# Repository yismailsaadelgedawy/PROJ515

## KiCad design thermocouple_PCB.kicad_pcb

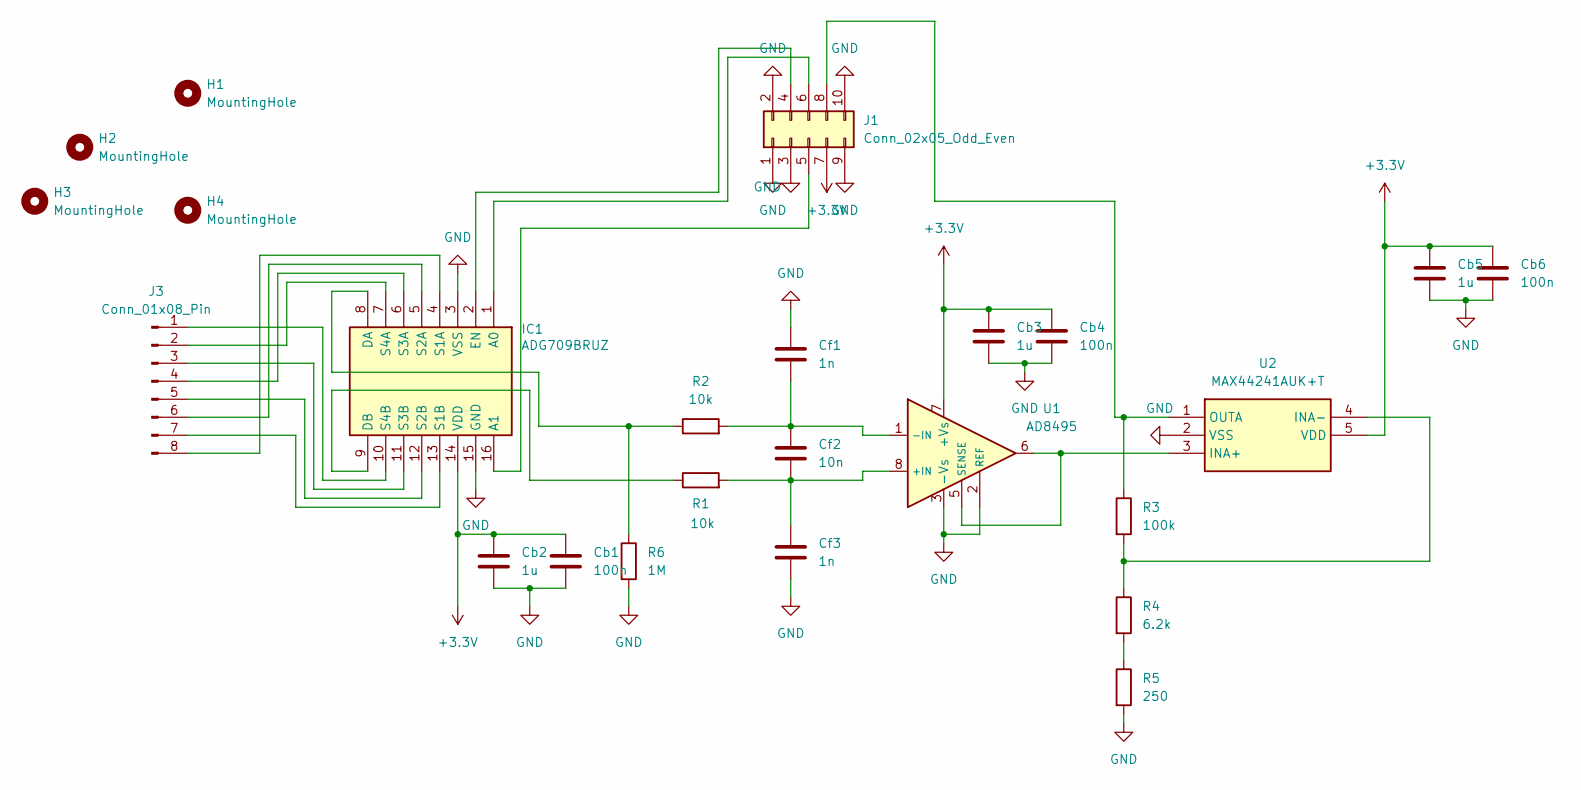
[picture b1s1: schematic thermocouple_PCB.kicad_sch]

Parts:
Cb1, Cb4, Cb6: 100n; C_0402_1005Metric
Cb2, Cb3, Cb5: 1u; C_0402_1005Metric
Cf1, Cf3: 1n; C_0603_1608Metric
Cf2: 10n; C_0603_1608Metric
H1, H2, H3, H4: MountingHole; MountingHole_2.2mm_M2_DIN965_Pad_TopBottom
IC1: ADG709BRUZ; TSSOP-16_4.4x5mm_P0.65mm; Manufacturer_Part_Number ADG709BRUZ; Mouser Part Number 584-ADG709BRUZ
J1: Conn_02x05_Odd_Even; PinHeader_2x05_P2.54mm_Horizontal
J3: Conn_01x08_Pin; PinHeader_1x08_P2.54mm_Horizontal
R1, R2: 10k; R_0402_1005Metric
R3: 100k; R_0402_1005Metric
R4: 6.2k; R_0603_1608Metric
R5: 250; R_0402_1005Metric
R6: 1M; R_0402_1005Metric
U1: AD8495; MSOP-8_3x3mm_P0.65mm
U2: MAX44241AUK+T; SOT-23-5; Manufacturer_Part_Number MAX44241AUK+T; Mouser Part Number 700-MAX44241AUK+T

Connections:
+3.3V: Cb1.1, Cb2.1, Cb3.1, Cb4.1, Cb5.1, Cb6.1, IC1.14 (VDD), J1.7, U1.7 (+Vs), U2.5 (VDD)
GND: Cb1.2, Cb2.2, Cb3.2, Cb4.2, Cb5.2, Cb6.2, Cf1.1, Cf3.2, IC1.3 (VSS), IC1.15 (GND), J1.1, J1.2, J1.3, J1.9, J1.10, R5.2, R6.2, U1.2 (REF), U1.3 (-Vs), U2.2 (VSS)
unnamed: IC1.1 (A0), J1.6
unnamed: IC1.16 (A1), J1.5
unnamed: IC1.8 (DA), R2.1, R6.1
unnamed: IC1.9 (DB), R1.1
unnamed: IC1.2 (EN), J1.4
unnamed: IC1.4 (S1A), J3.8
unnamed: IC1.13 (S1B), J3.7
unnamed: IC1.5 (S2A), J3.6
unnamed: IC1.12 (S2B), J3.5
unnamed: IC1.6 (S3A), J3.4
unnamed: IC1.11 (S3B), J3.3
unnamed: IC1.7 (S4A), J3.2
unnamed: IC1.10 (S4B), J3.1
unnamed: J1.8, R3.1, U2.1 (OUTA)
unnamed: R4.2, R5.1
unnamed: Cf2.2, Cf3.1, R1.2, U1.8 (+IN)
unnamed: Cf1.2, Cf2.1, R2.2, U1.1 (-IN)
unnamed: U1.5 (SENSE), U1.6, U2.3 (INA+)
unnamed: R3.2, R4.1, U2.4 (INA-)

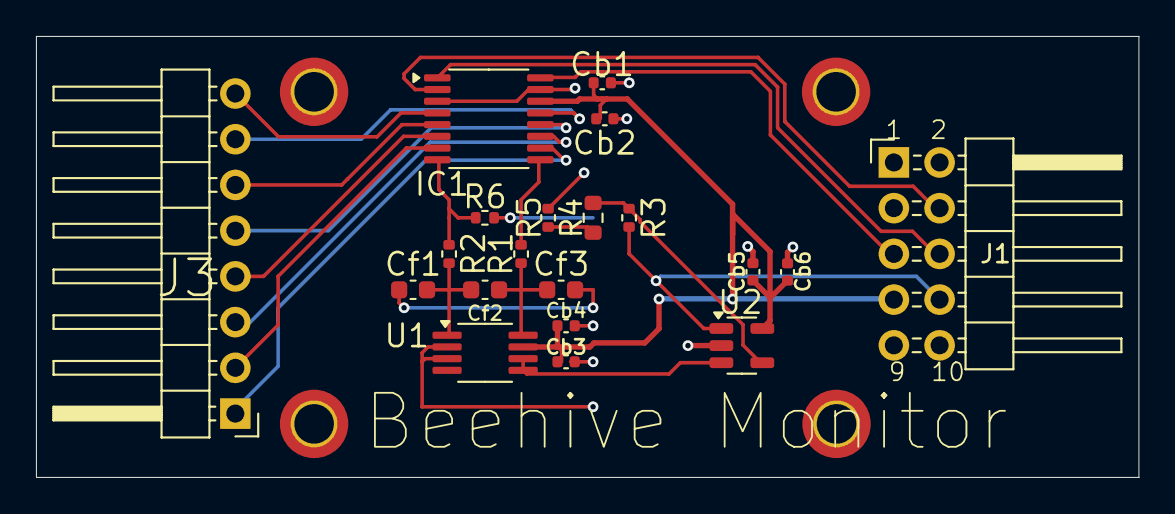
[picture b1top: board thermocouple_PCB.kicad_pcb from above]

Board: 2 copper layers, 61.2 x 24.5 mm, 24 parts (0 on the bottom side), 21 nets.

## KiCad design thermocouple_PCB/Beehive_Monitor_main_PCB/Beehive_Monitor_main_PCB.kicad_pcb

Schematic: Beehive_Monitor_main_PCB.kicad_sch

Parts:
5_V_PWR1, 12_V_PWR2: Conn_01x02_Pin; Molex_KK-254_AE-6410-02A_1x02_P2.54mm_Vertical
Accelerometer1: Conn_02x05_Odd_Even; PinHeader_2x05_P2.54mm_Vertical
C1: 22u; C_1206_3216Metric
C2, C11, C14, C25, C30, C35, C50, C51, C52, C101: 10u; C_0805_2012Metric
C3: 4.7u; C_1206_3216Metric
C4: 470n; C_0603_1608Metric
C5: 820p; C_0603_1608Metric_Pad1.08x0.95mm_HandSolder
C6: 68n; C_1206_3216Metric_Pad1.33x1.80mm_HandSolder
C7: 120p; C_0603_1608Metric_Pad1.08x0.95mm_HandSolder
C8, C9, C10, C18, C19, C20: 100u; C_1206_3216Metric
C12, C13, C24, C26, C32, C37, C41, C43, C45, C47, C49, C56, C80, C90, C92, C97, C98, C100, C103, C105, C107, C109, C114: 100n; C_0402_1005Metric
C15, C16, C17, C53, C54, C65, C72, C73, C74, C75, C76, C77: 15n; C_0805_2012Metric
C23, C40, C42, C44, C46, C48, C55, C57, C66, C78, C79, C81, C88, C89, C91, C93, C99, C102, C104, C106, C108, C110, C115: 1u; C_0402_1005Metric
C27, C33, C38: 3.3u; C_0603_1608Metric_Pad1.08x0.95mm_HandSolder
C28, C34, C39: 56p; C_0603_1608Metric_Pad1.08x0.95mm_HandSolder
C29, C31, C36: 2.2u; C_0603_1608Metric
C58, C59, C60, C61, C62, C63: 1.5n; C_0603_1608Metric
C64, C67, C69, C71: 1u; C_0402_1005Metric_Pad0.74x0.62mm_HandSolder
C68, C70: 100n; C_0402_1005Metric_Pad0.74x0.62mm_HandSolder
C82, C83, C84, C85, C86, C87, C111, C113, C116, C118: 10n; C_0603_1608Metric
C94, C96, C112, C117: 2.2n; C_0805_2012Metric
C95: 430p; C_0603_1608Metric_Pad1.08x0.95mm_HandSolder
Cboot1, Cboot5: 100n; C_0402_1005Metric
Css1, Css5: 2.2n; C_0805_2012Metric
D1, D2, D3, D4, D5, D7, D8: RBR2LAM60A; D_MELF
F1: Fuse; Fuseholder_Clip-5x20mm_Keystone_3517_Inline_P23.11x6.76mm_D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
IC1: LT6700HVCS6-3#PBF; TSOT-23-6; Manufacturer_Part_Number LT6700HVCS6-3#PBF
IC2, IC10: AD8226ARZ; SOIC-8_3.9x4.9mm_P1.27mm; Manufacturer_Part_Number AD8226ARZ; Mouser Part Number 584-AD8226ARZ
IC3, IC5: TPS54620RHLR; Texas_S-PVQFN-N14_ThermalVias; Manufacturer_Part_Number TPS54620RHLR; Mouser Part Number 595-TPS54620RHLR
IC4: AD8031ARTZ-R2; SOT-23-5; Manufacturer_Part_Number AD8031ARTZ-R2; Mouser Part Number 584-AD8031ARTZ-R2
IC6, IC7: MAX44246ASA+; MSOP-8_3x3mm_P0.65mm; Manufacturer_Part_Number MAX44246ASA+; Mouser Part Number 700-MAX44246ASA+
IC8: ADA4077-4ARZ; SOIC-14_3.9x8.7mm_P1.27mm; Manufacturer_Part_Number ADA4077-4ARZ; Mouser Part Number 584-ADA4077-4ARZ
IC9: SN74LV123ADRG4; TSSOP-16_4.4x5mm_P0.65mm; Manufacturer_Part_Number SN74LV123ADRG4; Mouser Part Number 595-SN74LV123ADRG4
IC11: TMUX1204DGSR; VSSOP-10_3x3mm_P0.5mm; Manufacturer_Part_Number TMUX1204DGSR; Mouser Part Number 595-TMUX1204DGSR
J1: Conn_02x08_Odd_Even; PinSocket_2x08_P2.54mm_Vertical_SMD
J2: Conn_02x10_Odd_Even; PinSocket_2x10_P2.54mm_Vertical_SMD
J3: Conn_02x15_Odd_Even; PinSocket_2x15_P2.54mm_Vertical_SMD
J4: Conn_02x17_Odd_Even; PinSocket_2x17_P2.54mm_Vertical_SMD
J5: Micro_SD_Card_Det_Hirose_DM3AT; microSD_HC_Hirose_DM3AT-SF-PEJM5
JP1: SolderJumper_2_Open; SolderJumper-2_P1.3mm_Open_RoundedPad1.0x1.5mm
JP3, JP4, JP5, JP7, JP8, JP9, JP10, JP11, JP12: SolderJumper_3_Bridged12; SolderJumper-3_P1.3mm_Bridged12_RoundedPad1.0x1.5mm
K2: HFD3_12-L2_257_; Relay_DPDT_Kemet_EC2_NU_DoubleCoil; Manufacturer_Part_Number HFD3/12-L2(257)
L1: 7443641000B; L_Wuerth_HCF-2818; Manufacturer_Part_Number 7443641000B; Mouser Part Number 710-7443641000B
L2: 22u; L_Wuerth_HCF-2818
L3: LMC555CMX_NOPB; SOIC-8_3.9x4.9mm_P1.27mm; Manufacturer_Part_Number LMC555CMX/NOPB; Mouser Part Number 926-LMC555CMX/NOPB
LCD_BTNs1: Conn_02x08_Odd_Even; PinHeader_2x08_P2.54mm_Vertical
LED_S1: Conn_02x05_Odd_Even; PinHeader_2x05_P2.54mm_Vertical
PE_9, PE_10, PE_15: SolderJumper_2_Open; SolderJumper-2_P1.3mm_Open_RoundedPad1.0x1.5mm
PF_14, PF_15: SolderJumper_2_Open; SolderJumper-2_P1.3mm_Open_RoundedPad1.0x1.5mm
PI_PWR1, PI_PWR2: Conn_01x02_Pin; Molex_KK-254_AE-6410-02A_1x02_P2.54mm_Vertical
PI_Ribbon1: Conn_02x05_Odd_Even; PinHeader_2x05_P2.54mm_Vertical
Q1, Q2, Q3, Q4, Q5, Q6, Q7: Q_NPN_BCE; SOT-23
Q8: PNP; SOT-23
Q9: FDS6681Z; SO-8_3.9x4.9mm_P1.27mm
R1, R3, R4, R17, R20, R28, R29, R30, R34, R35, R36, R39, R40, R41, R55, R72, R80, R87, R88, R105, R147, R148, R149, R500: 100k; R_0402_1005Metric
R2: 11.5k; R_0603_1608Metric_Pad0.98x0.95mm_HandSolder
R5, R73, R99, R103, R108, R123, R134, R140, R152, R169: 200; R_0402_1005Metric
R6, R15: 150k; R_0603_1608Metric
R7: 12k; R_0603_1608Metric_Pad0.98x0.95mm_HandSolder
R8, R119, R165, R175: 47k; R_0402_1005Metric
R9, R21, R44, R45, R96, R131, R168: 10k; R_0402_1005Metric
R10, R19: 3.9k; R_0603_1608Metric
R11: 330; R_0603_1608Metric
R12: 5.1k; R_0402_1005Metric
R13, R51: 150; R_0603_1608Metric
R14, R49, R65, R113, R129, R167: 12k; R_0603_1608Metric
R16: 909; R_0603_1608Metric_Pad0.98x0.95mm_HandSolder
R18, R89, R106, R151: 27k; R_0603_1608Metric
R22: 4.99k; R_0603_1608Metric
R23, R25, R42: 20k; R_0603_1608Metric_Pad0.98x0.95mm_HandSolder
R24, R26, R43: 5k; R_0603_1608Metric_Pad0.98x0.95mm_HandSolder
R27, R32, R37, R84, R92: 2.4k; R_0603_1608Metric
R31, R33, R38, R58, R68, R161, R172: 100; R_0603_1608Metric
R46: 1k; R_0402_1005Metric
R47, R116: 120k; R_0603_1608Metric
R48: 261k; R_0603_1608Metric_Pad0.98x0.95mm_HandSolder
R50, R81, R101, R157: 3k; R_0603_1608Metric
R52: 68.1k; R_0603_1608Metric_Pad0.98x0.95mm_HandSolder
R53: 37.4k; R_0603_1608Metric_Pad0.98x0.95mm_HandSolder
R54: 499; R_0603_1608Metric_Pad0.98x0.95mm_HandSolder
R56, R66, R82: 1.5k; R_0402_1005Metric
R57, R155, R160, R171: 2.2k; R_0603_1608Metric
R59: 56k; R_0603_1608Metric
R60, R162, R173: 75k; R_0603_1608Metric
R61, R90, R104: 470; R_0402_1005Metric
R62: 191k; R_0603_1608Metric_Pad0.98x0.95mm_HandSolder
R63: 41.7k; R_0603_1608Metric_Pad0.98x0.95mm_HandSolder
R64: 562; R_0603_1608Metric_Pad0.98x0.95mm_HandSolder
R67, R86, R91, R114, R164: 2k; R_0603_1608Metric
R69, R85, R95, R97, R132: 200k; R_0603_1608Metric
R70, R98, R133: 15k; R_0402_1005Metric
R71, R100, R135, R150: 1M; R_0402_1005Metric
R74, R111, R159, R163, R170, R174: 33k; R_0603_1608Metric
R75: 140k; R_0603_1608Metric_Pad0.98x0.95mm_HandSolder
R76: 1.2k; R_0603_1608Metric
R77, R145: 220; R_0603_1608Metric
R78: 316k; R_0603_1608Metric_Pad0.98x0.95mm_HandSolder
R79: 30k; R_0603_1608Metric
R83: 560; R_0603_1608Metric
R93, R136, R137: 220k; R_0603_1608Metric
R94, R156: 22k; R_0603_1608Metric
R102: 91k; R_0603_1608Metric_Pad0.98x0.95mm_HandSolder
R107: 6.34k; R_0603_1608Metric_Pad0.98x0.95mm_HandSolder
R109: 255k; R_0603_1608Metric_Pad0.98x0.95mm_HandSolder
R110, R141: 68k; R_0603_1608Metric
R112: 82k; R_0603_1608Metric
R115: 249; R_0603_1608Metric_Pad0.98x0.95mm_HandSolder
R117: 300k; R_0603_1608Metric
R118: 330k; R_0603_1608Metric
R120, R125, R126, R127, R138, R139, R142, R143: 4.7k; R_0402_1005Metric
R121, R130: 270; R_0603_1608Metric
R122: 80.6; R_0603_1608Metric_Pad0.98x0.95mm_HandSolder
R124: 4.32k; R_0603_1608Metric_Pad0.98x0.95mm_HandSolder
R128: 732k; R_0603_1608Metric_Pad0.98x0.95mm_HandSolder
R144, R146: 120; R_0402_1005Metric
R154: 6.2k; R_0603_1608Metric
R158: 18k; R_0603_1608Metric
R166, R176: 5.6k; R_0603_1608Metric
RV1, RV2: 5k; Potentiometer_Bourns_3296Y_Vertical
RV3, RV10, RV11: 50k; Potentiometer_Bourns_3296W_Vertical
RV4, RV5, RV6, RV7, RV8: 200k; Potentiometer_Bourns_3296W_Vertical
RV9: 25k; Potentiometer_Bourns_3296W_Vertical
TC_1_2, TC_3_4: Conn_02x07_Odd_Even; PinHeader_2x07_P2.54mm_Vertical
TP_1, TP_2, TP_3, TP_4, TP_5, TP_6, TP_7, TP_8, TP_9, TP_10: Conn_01x01_Pin; PinHeader_1x01_P2.54mm_Vertical
U1, U3, U4, U6, U7, U8: Opamp_Quad; SOIC-14_3.9x8.7mm_P1.27mm
U2, U5: TLV3201/2; SOIC-8_3.9x4.9mm_P1.27mm
mic_1_LDR1: Conn_01x04_Pin; Molex_KK-254_AE-6410-04A_1x04_P2.54mm_Vertical
mic_2: Conn_01x02_Pin; Molex_KK-254_AE-6410-02A_1x02_P2.54mm_Vertical

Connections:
3.3_V_out: C18.1, C19.1, C20.1, J1.8, K2.4 (COM_1), L2.2, LED_S1.10, PI_PWR2.1, R18.1; also elsewhere on the board
5_V: 5_V_PWR1.1, C8.1, C9.1, C10.1, C99.1, C100.1, D7.1 (K), D8.1 (K), IC9.2 (1B), IC9.3 (1~CLR), IC9.11 (2~CLR), IC9.16 (VCC), JP1.1 (A), K2.1 (SET+), K2.6 (RESET+), L1.1, LED_S1.4, LED_S1.6, PI_PWR1.1, Q8.3 (E), R8.1, R131.1, R136.1, R137.2, R144.1; also elsewhere on the board
6.11_kHz_AA_out_MCU: C63.2, D1.2 (A), J3.25, R63.2, R67.2, U1.14
6.11_kHz_out_MCU: J2.19, PI_Ribbon1.9, R71.2, U2.1; also elsewhere on the board
240_Hz_out_MCU: J2.11, PI_Ribbon1.1, R100.2, U2.7; also elsewhere on the board
555_out: L3.3 (OUTPUT), R146.1
Acc_420_Hz_out_MCU: J2.9, R135.2, U5.1
Acc_AA_out_to_MCU: C96.2, J3.2, U6.8, U6.9 (-)
Acc_sig_in: Accelerometer1.3, C35.1, C36.1; also elsewhere on the board
Acc_tmp: Accelerometer1.8, J4.12; also elsewhere on the board
BTN_1: J3.18, LCD_BTNs1.5; also elsewhere on the board
BTN_2: J3.20, LCD_BTNs1.3; also elsewhere on the board
BTN_3: J3.22, LCD_BTNs1.1; also elsewhere on the board
Cref: R72.1, RV7.3, TP_8.1, U2.2 (-), U2.6 (-)
Cref2: R167.1, RV8.3, TP_9.1, U5.2 (-)
D_4: J3.7, LCD_BTNs1.13; also elsewhere on the board
D_5: J3.5, LCD_BTNs1.11; also elsewhere on the board
D_6: J3.3, LCD_BTNs1.9; also elsewhere on the board
D_7: J3.1, LCD_BTNs1.7; also elsewhere on the board
EN: J4.20, LCD_BTNs1.12; also elsewhere on the board
Front_mic_pin: C30.1, C31.1, mic_1_LDR1.1; also elsewhere on the board
GND: 5_V_PWR1.2, 12_V_PWR2.2, Accelerometer1.9, C1.2, C2.2, C3.2, C4.2, C5.2, C6.2, C7.2, C8.2, C9.2, C10.2, C11.2, C12.2, C13.2, C14.2, C18.2, C19.2, C20.2, C23.2, C24.2, C26.2, C27.2, C32.2, C33.2, C37.2, C38.2, C40.2, C41.2, C42.2, C43.2, C44.2, C45.2, C46.2, C47.2, C48.2, C49.2, C50.2, C51.2, C52.2, C55.2, C56.2, C57.1, C64.2, C66.2, C67.2, C68.2, C69.2, C70.2, C71.1, C78.2, C79.2, C80.2, C81.1, C88.2, C89.2, C90.2, C91.2, C92.2, C99.2, C100.2, C101.2, C102.2, C103.2, C104.2, C105.2, C106.2, C107.2, C108.2, C109.2, C114.2, Css1.2, Css5.2, IC1.2 (GND), IC2.5 (-VS), IC2.6 (REF), IC3.2 (GND_1), IC3.3 (GND_2), IC3.15 (EP), IC4.2 (-VS), IC5.2 (GND_1), IC5.3 (GND_2), IC5.15 (EP), IC6.4 (GND), IC7.4 (GND), IC7.5 (INB+), IC8.11 (V-), IC9.8 (GND), IC9.9 (2~A), IC10.5 (-VS), IC10.6 (REF), IC11.3 (GND), J1.12, J1.14, J2.7, J3.11, J3.24, J4.6, J4.18, J4.21, J4.28, J5.6 (VSS), J5.11 (SHIELD), JP3.1 (A), JP4.1 (A), JP5.1 (A), JP7.1 (A), JP8.1 (A), JP9.1 (A), JP10.1 (A), JP11.1 (A), JP12.1 (A), L3.1 (GND), LCD_BTNs1.16, PI_PWR1.2, PI_PWR2.2, Q1.3 (E), Q2.3 (E), Q4.3 (E), Q5.3 (E), Q6.3 (E), R7.1, R9.2, R14.1, R20.2, R21.2, R29.2, R35.2, R40.2, R69.2, R97.2, R132.2, R145.2, R148.2, R152.2, RV1.2, RV2.2, RV7.2, RV8.2, RV9.2, RV11.2, TC_1_2.2, TC_1_2.13, TC_3_4.2, TC_3_4.13, U1.11 (V-), U2.4 (V-), U3.11 (V-), U4.11 (V-), U5.4 (V-), U6.11 (V-), U6.12 (+), U7.11 (V-), U7.12 (+), U8.11 (V-), U8.12 (+), mic_1_LDR1.2, mic_2.2; also elsewhere on the board
IC6_inA+: C32.1, C33.1, IC6.3 (INA+), R34.2, R35.1
IC6_inA-: C34.1, IC6.2 (INA-), R33.2, R36.1
IC6_inB+: C26.1, C27.1, IC6.5 (INB+), R28.2, R29.1
IC6_inB-: C28.1, IC6.6 (INB-), R30.1, R31.2
IC6_outA: C34.2, IC6.1 (OUTA), IC8.3 (+IN_A), R36.2
IC6_outB: C28.2, IC6.7 (OUTB), IC8.5 (+IN_B), R30.2
IC7_inA+: C37.1, C38.1, IC7.3 (INA+), R39.2, R40.1
IC7_inA-: C39.1, IC7.2 (INA-), R38.2, R41.1
IC7_outA: C39.2, IC7.1 (OUTA), IC8.10 (+IN_C), R41.2
LCD_B/light: J3.30, LCD_BTNs1.2; also elsewhere on the board
LDR_TRIG_out_MCU: J2.17, PI_Ribbon1.7, R150.2, U5.7; also elsewhere on the board
LDR_out_MCU: IC10.7 (VOUT), J3.12, R151.1, TP_10.1
LDR_pin_1: Accelerometer1.2, C23.1, C24.1, C40.1, C41.1, C42.1, C43.1, C44.1, C45.1, C48.1, C49.1, C55.1, C56.1, C66.1, C67.1, C68.1, C69.1, C70.1, C79.1, C80.1, C89.1, C90.1, C91.1, C92.1, C104.1, C105.1, C106.1, C107.1, C108.1, C109.1, C114.1, IC2.8 (+VS), IC4.5 (+VS), IC6.8 (VDD), IC7.8 (VDD), IC8.4 (V+), IC10.8 (+VS), IC11.5 (EN), IC11.6 (VDD), IC11.8 (D), J5.4 (VDD), K2.3 (NC_1), LCD_BTNs1.4, LCD_BTNs1.6, LCD_BTNs1.8, LCD_BTNs1.10, R4.1, R17.1, R28.1, R34.1, R39.1, R72.2, R110.2, R147.1, R149.1, TC_1_2.5, TC_1_2.10, TC_3_4.5, TC_3_4.10, U1.4 (V+), U2.8 (V+), U3.4 (V+), U4.4 (V+), U5.8 (V+), U6.4 (V+), U7.4 (V+), U8.4 (V+), mic_1_LDR1.3; also elsewhere on the board
LDR_pin_2: IC10.4 (+IN), RV9.1, TP_7.1, mic_1_LDR1.4; also elsewhere on the board
LNA_Acc_out: IC8.8 (OUT_C), RV6.1, TP_6.1, U4.3 (+), U6.3 (+)
LNA_MF_out: IC8.1 (OUT_A), R44.1, RV4.1, TP_4.1, U1.3 (+), U3.3 (+), U8.3 (+)
LNA_MR_out: IC8.7 (OUT_B), RV5.1, TP_5.1, U7.3 (+)
MCU_LED_IN: J3.21, R120.1, R125.1
MCU_TC_add_0: J1.13, TC_1_2.1, TC_1_2.14, TC_3_4.1, TC_3_4.14
MCU_TC_add_1: J1.15, TC_1_2.4, TC_1_2.11, TC_3_4.4, TC_3_4.11
MCU_TC_add_2: IC11.1 (A0), J3.26
MCU_TC_add_3: IC11.10 (A1), J3.28
M_LED_1_cathode: LED_S1.3, R121.1; also elsewhere on the board
M_LED_2_cathode: LED_S1.5, R130.1; also elsewhere on the board
Maintainance _int: J4.1, LED_S1.9, PI_Ribbon1.10; also elsewhere on the board
Mic_F_AA_out_to_MCU: C113.2, J3.4, U8.8, U8.9 (-)
Mic_R_AA_out_to_MCU: C118.2, J3.6, U7.8, U7.9 (-)
Mic_out_to_AA: IC8.14 (OUT_D), R45.1
unnamed: 12_V_PWR2.1, F1.1
unnamed: C4.1, R16.2
unnamed: C6.1, R11.2
unnamed: C15.1, C16.1, C76.1, C77.1, R89.1, R90.2
unnamed: C17.1, C53.1, C74.1, C75.1, R81.2, R82.1
unnamed: C17.2, C75.2, R86.2, R87.1, R88.2, U3.8
unnamed: C25.2, C29.2, R27.1
unnamed: C30.2, C31.2, R32.1
unnamed: C35.2, C36.2, R37.1
unnamed: C50.1, R24.2
unnamed: C51.1, R26.2
unnamed: C52.1, R43.2
unnamed: C54.1, C65.1, C72.1, C73.1, R75.2, R76.1
unnamed: C58.1, C59.1, R46.1, R47.2
unnamed: C59.2, R50.1, R52.1, U1.7
unnamed: C60.1, C61.1, R56.1, R57.2
unnamed: C61.2, R53.1, R59.2, R60.2, U1.8
unnamed: C62.1, C63.1, R61.2, R65.1
unnamed: C65.2, C73.2, R79.1, R80.1, U3.7
unnamed: C82.1, C83.1, R106.2, R107.1
unnamed: C83.2, R109.1, R111.1, U4.7
unnamed: C84.1, C85.1, R113.2, R114.1
unnamed: C85.2, R119.2, R122.2, U4.8
unnamed: C86.1, C87.1, R123.1, R124.2
unnamed: C96.1, R117.1, R157.2
unnamed: C113.1, R163.2, R165.1
unnamed: C118.1, R174.2, R175.1
unnamed: C64.1, D1.1 (K), R69.1, R70.1
unnamed: C16.2, C77.2, D2.2 (A), R94.2, R96.2, U3.14
unnamed: C78.1, D2.1 (K), R97.1, R98.1
unnamed: C87.2, D3.2 (A), R129.2, U4.14
unnamed: C88.1, D3.1 (K), R132.1, R133.1
unnamed: D5.2 (A), R146.2
unnamed: D7.2 (A), K2.12 (SET-), Q6.2 (C)
unnamed: D8.2 (A), K2.7 (RESET-), Q5.2 (C)
unnamed: IC1.3 (+INA), R13.2, RV1.3
unnamed: IC1.4 (+INB), R3.2, RV2.3
unnamed: IC2.2 (RG_1), RV3.2
unnamed: IC2.3 (RG_2), RV3.1
unnamed: Cboot5.1, IC3.13 (BOOT)
unnamed: C7.1, IC3.8 (COMP), R10.1
unnamed: Cboot5.2, IC3.11 (PH_1), IC3.12 (PH_2), L1.2
unnamed: IC3.1 (RT/CLK), R6.2
unnamed: Css5.1, IC3.9 (SS/TR)
unnamed: C11.1, C12.1, IC4.3 (+IN), R17.2, R20.1
unnamed: IC4.4 (-IN), R22.1
unnamed: Cboot1.1, IC5.13 (BOOT)
unnamed: C5.1, IC5.8 (COMP), R16.1
unnamed: Cboot1.2, IC5.11 (PH_1), IC5.12 (PH_2), L2.1
unnamed: IC5.1 (RT/CLK), R15.2
unnamed: Css1.1, IC5.9 (SS/TR)
unnamed: IC7.6 (INB-), IC7.7 (OUTB)
unnamed: IC8.2 (-IN_A), R23.2, R24.1
unnamed: IC8.6 (-IN_B), R25.2, R26.1
unnamed: IC8.9 (-IN_C), R42.2, R43.1
unnamed: IC8.13 (-IN_D), R44.2, R45.2
unnamed: C98.1, IC9.14 (1CEXT)
unnamed: C98.2, IC9.15 (1REXT/CEXT), R137.1
unnamed: IC9.1 (1~A), IC9.10 (2B), Q3.2 (C), R131.2
unnamed: C97.2, IC9.6 (2CEXT)
unnamed: C97.1, IC9.7 (2REXT/CEXT), R136.2
unnamed: IC10.1 (-IN), R147.2, R148.1
unnamed: IC10.2 (RG_1), RV10.1
unnamed: IC10.3 (RG_2), RV10.2
unnamed: J1.10, JP1.2 (B)
unnamed: J4.3, PE_9.1 (A)
unnamed: J4.7, PF_14.1 (A)
unnamed: J4.11, PF_15.1 (A)
unnamed: J4.23, PE_10.1 (A)
unnamed: J4.29, PE_15.1 (A)
unnamed: C110.2, JP3.2 (C)
unnamed: C111.2, JP4.2 (C)
unnamed: C115.2, JP5.2 (C)
unnamed: C112.2, JP7.2 (C)
unnamed: C116.2, JP8.2 (C)
unnamed: C117.2, JP9.2 (C)
unnamed: C93.2, JP10.2 (C)
unnamed: C94.2, JP11.2 (C)
unnamed: C95.2, JP12.2 (C)
unnamed: L3.7 (DISCHARGE), R141.1, R169.2
unnamed: C101.1, L3.2 (~TRIGGER), L3.6 (THRESHOLD), R164.2
unnamed: Q1.1 (B), R120.2
unnamed: Q1.2 (C), R121.2
unnamed: Q2.1 (B), R126.2
unnamed: Q2.2 (C), R130.2
unnamed: Q3.1 (B), R125.2
unnamed: Q3.3 (E), Q4.2 (C)
unnamed: Q4.1 (B), R127.2
unnamed: Q5.1 (B), R139.2
unnamed: Q6.1 (B), R138.2
unnamed: Q7.1 (B), R142.2
unnamed: Q7.2 (C), R144.2
unnamed: Q8.2 (B), R143.2
unnamed 144: F1.2, Q9.1 (D); also elsewhere on the board
unnamed: Q9.2 (G), R152.1
unnamed: R6.1, R7.2
unnamed: R10.2, R11.1
unnamed: R8.2, R12.1
unnamed: R5.1, R12.2
unnamed: R2.2, R13.1
unnamed: R14.2, R15.1
unnamed: R18.2, R19.1
unnamed: R23.1, RV4.2
unnamed: R25.1, RV5.2
unnamed: R27.2, R31.1
unnamed: R32.2, R33.1
unnamed: R37.2, R38.1
unnamed: R42.1, RV6.2
unnamed: R46.2, R51.2
unnamed: R47.1, R49.2
unnamed: R48.1, R50.2
unnamed: R52.2, R57.1
unnamed: R55.2, R59.1
unnamed: R56.2, R58.1
unnamed: R60.1, R65.2
unnamed: R61.1, R66.2
unnamed: R62.2, R67.1
unnamed: R63.1, R68.2
unnamed: R70.2, R73.1
unnamed: R74.2, R75.1
unnamed: R76.2, R77.2
unnamed: R78.1, R79.2
unnamed: R82.2, R83.1
unnamed: R85.2, R86.1
unnamed: R88.1, R89.2
unnamed: R90.1, R91.2
unnamed: R93.2, R94.1
unnamed: R95.2, R96.1
unnamed: R98.2, R99.1
unnamed: R80.2, R101.1
unnamed: R81.1, R101.2
unnamed: R87.2, R102.1
unnamed: R84.2, R103.1
unnamed: R92.1, R104.2
unnamed: R105.2, R106.1
unnamed: R107.2, R108.2
unnamed: R110.1, R167.2
unnamed: R111.2, R113.1
unnamed: R112.2, R154.1
unnamed: R114.2, R115.1
unnamed: R116.2, R156.1
unnamed: R117.2, R158.1
unnamed: R118.2, R168.1
unnamed: R119.1, R168.2
unnamed: R122.1, R123.2
unnamed: R128.2, R129.1
unnamed: R133.2, R134.1
unnamed: R140.2, R169.1
unnamed: R141.2, R164.1
unnamed: R154.2, R155.1
unnamed: R156.2, R157.1
unnamed: R159.2, R160.1
unnamed: R160.2, R161.1
unnamed: R162.2, R163.1
unnamed: R165.2, R166.1
unnamed: R170.2, R171.1
unnamed: R171.2, R172.1
unnamed: R173.2, R174.1
unnamed: R175.2, R176.1
unnamed: C57.2, R49.1, U1.1, U1.2 (-)
unnamed: C58.2, R48.2, U1.6 (-)
unnamed: R53.2, R54.1, U1.10 (+)
unnamed: C60.2, R55.1, U1.9 (-)
unnamed: R64.2, R68.1, U1.12 (+)
unnamed: C62.2, R62.1, U1.13 (-)
unnamed: R71.1, R73.2, U2.3 (+)
unnamed: R99.2, R100.1, U2.5 (+)
unnamed: C71.2, R74.1, U3.1, U3.2 (-)
unnamed: C54.2, C72.2, R78.2, U3.6 (-)
unnamed: R84.1, R102.2, U3.10 (+)
unnamed: C53.2, C74.2, R85.1, U3.9 (-)
unnamed: R92.2, R95.1, U3.12 (+)
unnamed: C15.2, C76.2, R93.1, U3.13 (-)
unnamed: C81.2, R105.1, U4.1, U4.2 (-)
unnamed: C82.2, R109.2, U4.6 (-)
unnamed: C84.2, R118.1, U4.9 (-)
unnamed: C86.2, R128.1, U4.13 (-)
unnamed: R134.2, R135.1, U5.3 (+)
unnamed: R150.1, R151.2, U5.5 (+)
unnamed: R149.2, RV11.1, U5.6 (-)
unnamed: C93.1, R112.1, U6.1, U6.2 (-)
unnamed: C94.1, R155.2, U6.5 (+)
unnamed: R116.1, U6.6 (-), U6.7
unnamed: C95.1, R158.2, U6.10 (+)
unnamed: U6.13 (-), U6.14
unnamed: C115.1, R170.1, U7.1, U7.2 (-)
unnamed: C116.1, R172.2, U7.5 (+)
unnamed: R173.1, U7.6 (-), U7.7
unnamed: C117.1, R176.2, U7.10 (+)
unnamed: U7.13 (-), U7.14
unnamed: C110.1, R159.1, U8.1, U8.2 (-)
unnamed: C111.1, R161.2, U8.5 (+)
unnamed: R162.1, U8.6 (-), U8.7
unnamed: C112.1, R166.2, U8.10 (+)
unnamed: U8.13 (-), U8.14
PI_CS: J4.5, PI_Ribbon1.8; also elsewhere on the board
PI_LED_IN: PI_Ribbon1.3, R126.1, R127.1; also elsewhere on the board
PI_MISO: J4.9, PI_Ribbon1.6; also elsewhere on the board
PI_MOSI: J4.27, PI_Ribbon1.2; also elsewhere on the board
PI_SCLK: J4.25, PI_Ribbon1.4; also elsewhere on the board
Pwr_LED_Anode: D4.1 (K), D5.1 (K), LED_S1.2; also elsewhere on the board
Pwr_LED_Cathode: LED_S1.1, R145.1; also elsewhere on the board
RS: J4.24, LCD_BTNs1.14; also elsewhere on the board
RW: J4.22, LCD_BTNs1.15; also elsewhere on the board
Rear_mic_pin: C25.1, C29.1, mic_2.1; also elsewhere on the board
Relay_close: IC9.5 (2Q), R139.1
Relay_open: IC9.13 (1Q), R138.1
SD_CS: J2.14, J5.2 (DAT3/CD)
SD_MISO: J2.20, J5.7 (DAT0)
SD_MOSI: J2.16, J5.3 (CMD)
SD_SCLK: J2.18, J5.5 (CLK)
SD__detect: J4.16, J5.9 (DET_B), J5.10 (DET_A)
TC_EN_1: IC11.2 (S1), TC_1_2.3
TC_EN_2: IC11.9 (S2), TC_1_2.12
TC_EN_3: IC11.4 (S3), TC_3_4.3
TC_EN_4: IC11.7 (S4), TC_3_4.12
TC_Sig_1: J3.10, TC_1_2.6, TC_1_2.9, TC_3_4.6, TC_3_4.9
V_555: C102.1, C103.1, L3.4 (~RESET), L3.8 (V+), Q8.1 (C), R140.1
V_LED: D4.2 (A), Q7.3 (E)
Vcharge_MCU: IC2.7 (VOUT), J3.8, TP_3.1
Ven: IC1.6 (OUTB), IC3.10 (EN), IC5.10 (EN), R500.2, TP_1.1
Vref: C13.1, C14.1, IC2.4 (+IN), IC4.1 (VOUT), IC8.12 (+IN_D), JP3.3 (B), JP4.3 (B), JP5.3 (B), JP7.3 (B), JP8.3 (B), JP9.3 (B), JP10.3 (B), JP11.3 (B), JP12.3 (B), R22.2, R51.1, R54.2, R58.2, R64.1, R66.1, R77.1, R83.2, R91.1, R103.2, R104.1, R108.1, R115.2, R124.1, U1.5 (+), U3.5 (+), U4.5 (+), U4.10 (+), U4.12 (+)
Vreg_in: C1.1, C2.1, C3.1, C46.1, C47.1, IC1.5 (VS), IC3.4 (PVIN_1), IC3.5 (PVIN_2), IC3.6 (VIN), IC5.4 (PVIN_1), IC5.5 (PVIN_2), IC5.6 (VIN), Q9.3 (S), R1.1, R3.1
Vsens_3.3: IC5.7 (VSENSE), R19.2, R21.1
Vsens_5: IC3.7 (VSENSE), R5.2, R9.1
Vt_bat_trig_MCU: IC1.1 (OUTA), J2.15, PI_Ribbon1.5, R4.2, R142.1, R143.1, TP_2.1; also elsewhere on the board
Vtest: IC2.1 (-IN), R1.2, R2.1, R500.1

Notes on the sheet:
consider changing R2 for pot?
3.3 V regulator
240 Hz bandpass trigger
10 uH
6.11 kHz bandpass trigger
Colour code: Blue GPIO pin orange external componant wire cyan interrupt pin magenta ADC pin
Input and charge monitoring
800 Hz AA filter
Maintenance circuit
Power LED circuit
RS supplied L1
Reference voltage
LDR circuit
450 Hz AA filter
Farnell supplied C6 C7 L2 R2 R16 R48 R52 R53 R54 C5 C23 C28 R62 R75 R78 R107 R109 R118 R122 R128
420 Hz bandpass trigger
Microphone and accelerometer amplifiers
Thermocouple frame selection
5 V regulator

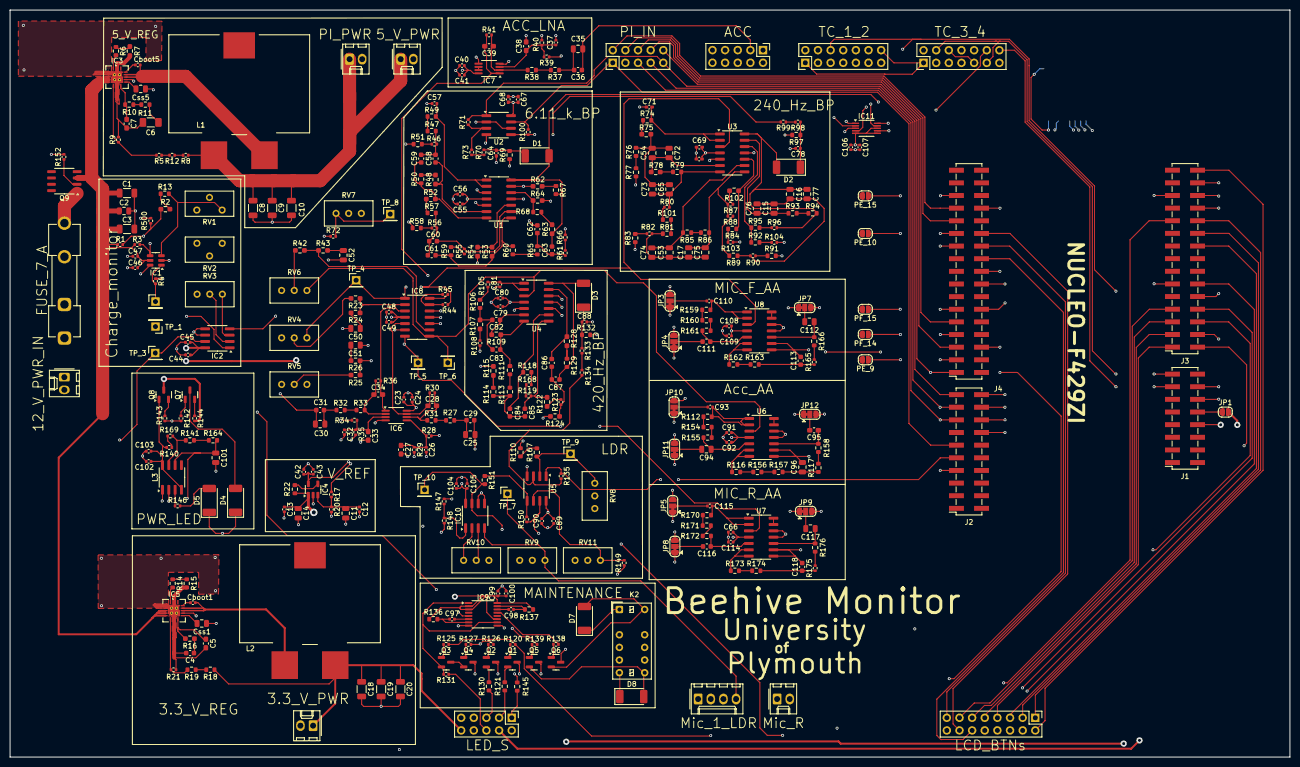
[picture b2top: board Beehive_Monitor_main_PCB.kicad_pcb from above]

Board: 4 copper layers, 257.2 x 150.1 mm, 389 parts (1 on the bottom side), 277 nets.

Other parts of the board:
3.3_V_PWR, 5_V_PWR, 12_V_PWR_IN: Conn_01x02_Pin; Molex_KK-254_AE-6410-02A_1x02_P2.54mm_Vertical
ACC: Conn_02x05_Odd_Even; PinHeader_2x05_P2.54mm_Vertical
FUSE_7_A: Fuse; Fuseholder_Clip-5x20mm_Keystone_3517_Inline_P23.11x6.76mm_D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
LCD_BTNs: Conn_02x08_Odd_Even; PinHeader_2x08_P2.54mm_Vertical
LED_S: Conn_02x05_Odd_Even; PinHeader_2x05_P2.54mm_Vertical
Mic_1_LDR: Conn_01x04_Pin; Molex_KK-254_AE-6410-04A_1x04_P2.54mm_Vertical
Mic_R: Conn_01x02_Pin; Molex_KK-254_AE-6410-02A_1x02_P2.54mm_Vertical
PI_IN: Conn_02x05_Odd_Even; PinHeader_2x05_P2.54mm_Vertical
PI_PWR: Conn_01x02_Pin; Molex_KK-254_AE-6410-02A_1x02_P2.54mm_Vertical

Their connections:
3.3_V_out: 3.3_V_PWR.1, LED_S.10; also elsewhere on the board
5_V: 5_V_PWR.1, LED_S.4, LED_S.6, PI_PWR.1; also elsewhere on the board
6.11_kHz_out_MCU: PI_IN.9; also elsewhere on the board
12 V_in: 12_V_PWR_IN.1, FUSE_7_A.1
240_Hz_out_MCU: PI_IN.1; also elsewhere on the board
Acc_sig_in: ACC.3; also elsewhere on the board
Acc_tmp: ACC.8; also elsewhere on the board
BTN_1: LCD_BTNs.5; also elsewhere on the board
BTN_2: LCD_BTNs.3; also elsewhere on the board
BTN_3: LCD_BTNs.1; also elsewhere on the board
D_4: LCD_BTNs.13; also elsewhere on the board
D_5: LCD_BTNs.11; also elsewhere on the board
D_6: LCD_BTNs.9; also elsewhere on the board
D_7: LCD_BTNs.7; also elsewhere on the board
EN: LCD_BTNs.12; also elsewhere on the board
Front_mic_pin: Mic_1_LDR.1; also elsewhere on the board
GND: 3.3_V_PWR.2, 5_V_PWR.2, 12_V_PWR_IN.2, ACC.9, LCD_BTNs.16, Mic_1_LDR.2, Mic_R.2, PI_PWR.2; also elsewhere on the board
LCD_B/light: LCD_BTNs.2; also elsewhere on the board
LDR_TRIG_out_MCU: PI_IN.7; also elsewhere on the board
LDR_pin_1: ACC.2, LCD_BTNs.4, LCD_BTNs.6, LCD_BTNs.8, LCD_BTNs.10, Mic_1_LDR.3; also elsewhere on the board
LDR_pin_2: Mic_1_LDR.4; also elsewhere on the board
M_LED_1_cathode: LED_S.3; also elsewhere on the board
M_LED_2_cathode: LED_S.5; also elsewhere on the board
Maintainance _int: LED_S.9, PI_IN.10; also elsewhere on the board
unnamed 144: FUSE_7_A.2; also elsewhere on the board
PI_CS: PI_IN.8; also elsewhere on the board
PI_LED_IN: PI_IN.3; also elsewhere on the board
PI_MISO: PI_IN.6; also elsewhere on the board
PI_MOSI: PI_IN.2; also elsewhere on the board
PI_SCLK: PI_IN.4; also elsewhere on the board
Pwr_LED_Anode: LED_S.2; also elsewhere on the board
Pwr_LED_Cathode: LED_S.1; also elsewhere on the board
RS: LCD_BTNs.14; also elsewhere on the board
RW: LCD_BTNs.15; also elsewhere on the board
Rear_mic_pin: Mic_R.1; also elsewhere on the board
Vt_bat_trig_MCU: PI_IN.5; also elsewhere on the board

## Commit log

2024-11-12 added block diagram file
    using draw.io
2024-11-13 Update to include Comp Vision information
2024-11-14 Create Gantt Mermaid
2024-11-15 Update Gantt Mermaid
    Prev wasn't actually the Gantt
2025-01-29 Created using Colab
2025-02-03 implemented simple DFT
    unoptimised, but works;
    still need to test its real-time functionality using a sensor
2025-02-04 implemented DFT with sensor readings
    uses the mic on the MSB for now to test;
    still needs some work
2025-02-04 optimised DFT
    applied coefficient symmetry;
    runs 2x as fast;
    uses 1/2 the memory;
    still needs:
    window function
    FFT form
2025-02-05 [WIP] FFT implmentation
    almost there...
2025-02-05 First working version of FFT
2025-02-05 FFT implemented
2025-02-06 updated FFT
    fixed my old algorithm
2025-02-06 Major optimisations to the FFT algorithm
    reduced memory usage
    increased processing speed
2025-02-06 added a few comments
2025-02-06 comments + cleaner code
2025-02-07 cleaned up FFT code
    also added comments.
    Algorithm done now.
2025-02-09 optimised FFT further
    halved the number of multiplications from 2 to 1
    Nlog(N) -> (N/2l)og(N)
    faster by approx. 4ms
2025-02-10 [WIP] implemented piping detection
    still need to add a few more features to make it complete
2025-02-10 added comments
    comments + cleanup
2025-02-10 added important comment
    explained the conditions to achieve a detection threshold of 1000
2025-02-12 completed piping detection
    • Implemented rising edge detection for pulse detection for short pulses (fixed bug where it was not detecting a pulse, rather just the level). Used off threshold to prevent "jitter" around single th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
    • Automatically determined loop time at the start of program
    • Parameterised everything
    • Dealt with following condition: long pulse, but no short pulse; reset after timeout
    • Disabled averaging in short pulse window to make it more responsive; pulses are short in time
    Bug fixes!
2025-02-12 implemented basic temperature sensing
    beginning of brood area mapping
2025-02-13 best.pt of training done with yolov8n
2025-02-13 Testing video 1
2025-02-24 added example program for RTC
2025-02-25 [WIP] some RTC functionality implemented
    * added unix timestamp algorithm
    * added LCD code
    * [WIP] user input of date and time using buttons and LCD for output
2025-02-25 RTC and related components fully implemented
2025-02-26 added example SD card functionality
    used for logging
2025-02-26 added important comments
    on SD program
2025-02-26 fixing bug
2025-02-26 fixing bug...
2025-03-03 added pin mappings list
2025-03-09 PCB files added
2025-03-11 latest pcb files
2025-03-25 mcu analogue pins doc added
2025-03-26 copy files
2025-03-27 Sort Testing
2025-03-28 implemented brood area mapping
2025-04-06 Create Detect_Or_Track_Bee_Logging
    Integration of bee specific tracking/counting components, wasp tracking + Headless run mode implementation for efficiency
2025-04-06 Create detect_or_track_bee_pollen_logging
    Tracks and logs bees movement + wasps + Pollen Clustering using K Means (Currently CSV Output)
2025-04-12 Logging with Firebase integration
2025-04-13 Dual Camera test
2025-04-21 Create 4byte_mcu.c
    sends 4 dummy bytes from mcu to pi
2025-04-21 Create 4byte_pi.py
    pi code to receive 4 bytes from mcu and send back dummy bytes
2025-04-28 updated code
2025-04-29 fixed blunder
2025-04-29 added SPI code
2025-04-29 finalised hornet detection alg
2025-04-29 finalised acc alg
2025-04-29 Merged code into one file
    finally...
2025-04-30 merged
2025-04-30 updated merge
